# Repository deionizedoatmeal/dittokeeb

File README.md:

# dittokeeb
RP2040 powered keyboard!

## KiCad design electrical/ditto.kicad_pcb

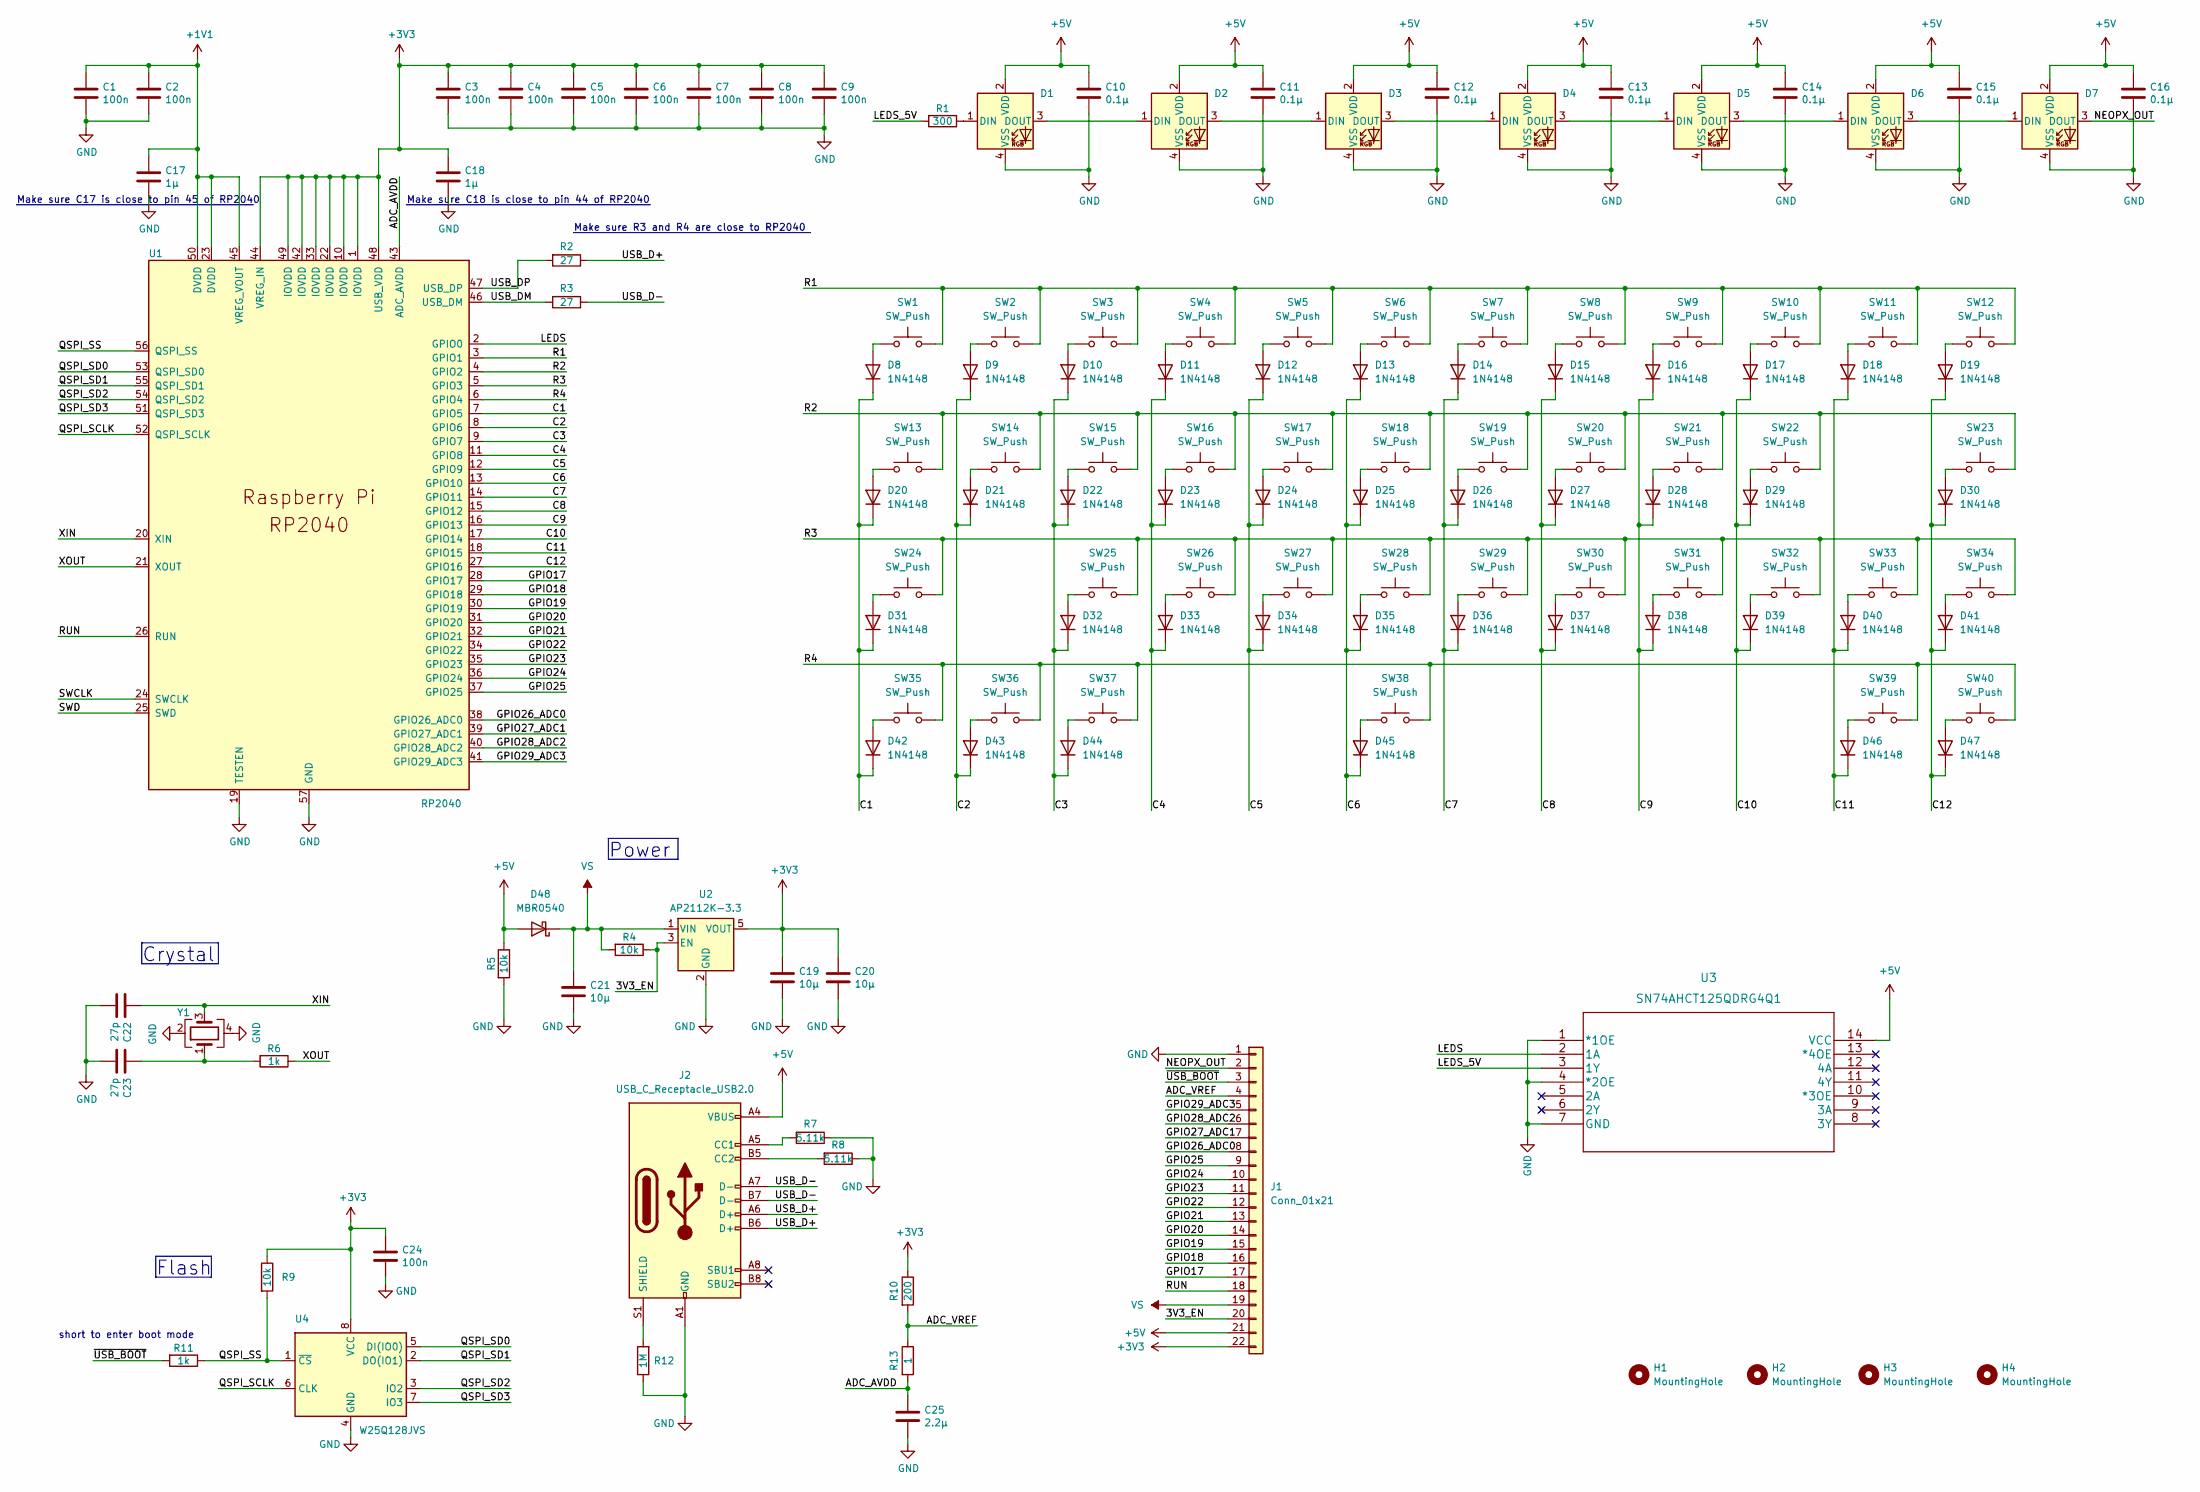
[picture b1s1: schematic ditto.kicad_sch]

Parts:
C1, C2, C3, C4, C5, C6, C7, C8, C9, C24: 100n; C_0402_1005Metric
C10, C11, C12, C13, C14, C15, C16: 0.1µ; C_0805_2012Metric
C17, C18: 1µ; C_0402_1005Metric
C19, C20, C21: 10µ; C_0805_2012Metric
C22, C23: 27p; C_0402_1005Metric
C25: 2.2µ; C_0402_1005Metric
D1, D2, D3, D4, D5, D6, D7: SK6805-EC
D8, D9, D10, D11, D12, D13, D14, D15, D16, D17, D18, D19, D20, D21, D22, D23, D24, D25, D26, D27, D28, D29, D30, D31, D32, D33, D34, D35, D36, D37, D38, D39, D40, D41, D42, D43, D44, D45, D46, D47: 1N4148; D_DO-35_SOD27_P7.62mm_Horizontal
D48: MBR0540; D_SOD-123
H1, H2, H3, H4: MountingHole; MountingHole_2.2mm_M2_DIN965_Pad
J1: Conn_01x21; PinHeader_1x22_P1.00mm_Horizontal
J2: USB_C_Receptacle_USB2.0; USB_C_Receptacle_HRO_TYPE-C-31-M-12
R1: 300; R_0603_1608Metric
R2, R3: 27; C_0402_1005Metric
R4, R5, R9: 10k; C_0402_1005Metric
R6, R11: 1k; C_0402_1005Metric
R7, R8: 5.11k; C_0402_1005Metric
R10: 200; C_0402_1005Metric
R12: 1M; C_0402_1005Metric
R13: 1; C_0402_1005Metric
SW1, SW2, SW3, SW4, SW5, SW6, SW7, SW8, SW9, SW10, SW11, SW12, SW14, SW15, SW16, SW17, SW18, SW19, SW20, SW21, SW22, SW25, SW26, SW27, SW28, SW29, SW30, SW31, SW32, SW34, SW36, SW37: SW_Push; SW_Cherry_MX_1.00u_PCB
SW13, SW33, SW35, SW39, SW40: SW_Push; SW_Cherry_MX_1.25u_PCB
SW23, SW24: SW_Push; SW_Cherry_MX_1.75u_PCB
SW38: SW_Push; SW_Cherry_MX_6.25u_PCB
U1: RP2040; RP2040-QFN-56
U2: AP2112K-3.3; SOT-23-5
U3: SN74AHCT125QDRG4Q1
U4: W25Q128JVS; SOIC-8_5.23x5.23mm_P1.27mm
Y1: Crystal_GND24; Crystal_SMD_3225-4Pin_3.2x2.5mm

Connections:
+1V1: C1.1, C2.1, C17.1, U1.23 (DVDD), U1.45 (VREG_VOUT), U1.50 (DVDD)
+3V3: C3.1, C4.1, C5.1, C6.1, C7.1, C8.1, C9.1, C18.1, C19.1, C20.1, C24.1, J1.22, R9.1, R10.1, U1.1 (IOVDD), U1.10 (IOVDD), U1.22 (IOVDD), U1.33 (IOVDD), U1.42 (IOVDD), U1.44 (VREG_IN), U1.48 (USB_VDD), U1.49 (IOVDD), U2.5 (VOUT), U4.8 (VCC)
+5V: C10.1, C11.1, C12.1, C13.1, C14.1, C15.1, C16.1, D1.2 (VDD), D2.2 (VDD), D3.2 (VDD), D4.2 (VDD), D5.2 (VDD), D6.2 (VDD), D7.2 (VDD), D48.2 (A), J1.21, J2.A4 (VBUS), J2.A9 (VBUS), J2.B4 (VBUS), J2.B9 (VBUS), R5.1, U3.14 (VCC)
/3V3_EN: J1.20, R4.1, U2.3 (EN)
/ADC_AVDD: C25.1, R13.2, U1.43 (ADC_AVDD)
/ADC_VREF: J1.4, R10.2, R13.1
/C1: D8.1 (K), D20.1 (K), D31.1 (K), D42.1 (K), U1.7 (GPIO5)
/C2: D9.1 (K), D21.1 (K), D43.1 (K), U1.8 (GPIO6)
/C3: D10.1 (K), D22.1 (K), D32.1 (K), D44.1 (K), U1.9 (GPIO7)
/C4: D11.1 (K), D23.1 (K), D33.1 (K), U1.11 (GPIO8)
/C5: D12.1 (K), D24.1 (K), D34.1 (K), U1.12 (GPIO9)
/C6: D13.1 (K), D25.1 (K), D35.1 (K), D45.1 (K), U1.13 (GPIO10)
/C7: D14.1 (K), D26.1 (K), D36.1 (K), U1.14 (GPIO11)
/C8: D15.1 (K), D27.1 (K), D37.1 (K), U1.15 (GPIO12)
/C9: D16.1 (K), D28.1 (K), D38.1 (K), U1.16 (GPIO13)
/C10: D17.1 (K), D29.1 (K), D39.1 (K), U1.17 (GPIO14)
/C11: D18.1 (K), D40.1 (K), D46.1 (K), U1.18 (GPIO15)
/C12: D19.1 (K), D30.1 (K), D41.1 (K), D47.1 (K), U1.27 (GPIO16)
/GPIO17: J1.17, U1.28 (GPIO17)
/GPIO18: J1.16, U1.29 (GPIO18)
/GPIO19: J1.15, U1.30 (GPIO19)
/GPIO20: J1.14, U1.31 (GPIO20)
/GPIO21: J1.13, U1.32 (GPIO21)
/GPIO22: J1.12, U1.34 (GPIO22)
/GPIO23: J1.11, U1.35 (GPIO23)
/GPIO24: J1.10, U1.36 (GPIO24)
/GPIO25: J1.9, U1.37 (GPIO25)
/GPIO26_ADC0: J1.8, U1.38 (GPIO26_ADC0)
/GPIO27_ADC1: J1.7, U1.39 (GPIO27_ADC1)
/GPIO28_ADC2: J1.6, U1.40 (GPIO28_ADC2)
/GPIO29_ADC3: J1.5, U1.41 (GPIO29_ADC3)
/LEDS: U1.2 (GPIO0), U3.2 (1A)
/LEDS_5V: R1.2, U3.3 (1Y)
/NEOPX_OUT: D7.3 (DOUT), J1.2
/QSPI_SCLK: U1.52 (QSPI_SCLK), U4.6 (CLK)
/QSPI_SD0: U1.53 (QSPI_SD0), U4.5 (DI(IO0))
/QSPI_SD1: U1.55 (QSPI_SD1), U4.2 (DO(IO1))
/QSPI_SD2: U1.54 (QSPI_SD2), U4.3 (IO2)
/QSPI_SD3: U1.51 (QSPI_SD3), U4.7 (IO3)
/QSPI_SS: R9.2, R11.1, U1.56 (QSPI_SS), U4.1 (~CS)
/R1: SW1.2, SW2.2, SW3.2, SW4.2, SW5.2, SW6.2, SW7.2, SW8.2, SW9.2, SW10.2, SW11.2, SW12.2, U1.3 (GPIO1)
/R2: SW13.2, SW14.2, SW15.2, SW16.2, SW17.2, SW18.2, SW19.2, SW20.2, SW21.2, SW22.2, SW23.2, U1.4 (GPIO2)
/R3: SW24.2, SW25.2, SW26.2, SW27.2, SW28.2, SW29.2, SW30.2, SW31.2, SW32.2, SW33.2, SW34.2, U1.5 (GPIO3)
/R4: SW35.2, SW36.2, SW37.2, SW38.2, SW39.2, SW40.2, U1.6 (GPIO4)
/RUN: J1.18, U1.26 (RUN)
/SWCLK: U1.24 (SWCLK)
/SWD: U1.25 (SWD)
/USB_D+: J2.A6 (D+), J2.B6 (D+), R2.1
/USB_D-: J2.A7 (D-), J2.B7 (D-), R3.1
/USB_DM: R3.2, U1.46 (USB_DM)
/USB_DP: R2.2, U1.47 (USB_DP)
/XIN: C22.1, U1.20 (XIN), Y1.3
/XOUT: R6.1, U1.21 (XOUT)
/~USB_BOOT: J1.3, R11.2
GND: C1.2, C2.2, C3.2, C4.2, C5.2, C6.2, C7.2, C8.2, C9.2, C10.2, C11.2, C12.2, C13.2, C14.2, C15.2, C16.2, C17.2, C18.2, C19.2, C20.2, C21.2, C22.2, C23.2, C24.2, C25.2, D1.4 (VSS), D2.4 (VSS), D3.4 (VSS), D4.4 (VSS), D5.4 (VSS), D6.4 (VSS), D7.4 (VSS), J1.1, J2.A1 (GND), J2.A12 (GND), J2.B1 (GND), J2.B12 (GND), R5.2, R7.1, R8.1, R12.1, U1.19 (TESTEN), U1.57 (GND), U2.2 (GND), U3.1 (*1OE), U3.4 (*2OE), U3.7 (GND), U4.4 (GND), Y1.2, Y1.4
unnamed: C23.1, R6.2, Y1.1
unnamed: D1.1 (DIN), R1.1
unnamed: D1.3 (DOUT), D2.1 (DIN)
unnamed: D2.3 (DOUT), D3.1 (DIN)
unnamed: D3.3 (DOUT), D4.1 (DIN)
unnamed: D4.3 (DOUT), D5.1 (DIN)
unnamed: D5.3 (DOUT), D6.1 (DIN)
unnamed: D6.3 (DOUT), D7.1 (DIN)
unnamed: D8.2 (A), SW1.1
unnamed: D9.2 (A), SW2.1
unnamed: D10.2 (A), SW3.1
unnamed: D11.2 (A), SW4.1
unnamed: D12.2 (A), SW5.1
unnamed: D13.2 (A), SW6.1
unnamed: D14.2 (A), SW7.1
unnamed: D15.2 (A), SW8.1
unnamed: D16.2 (A), SW9.1
unnamed: D17.2 (A), SW10.1
unnamed: D18.2 (A), SW11.1
unnamed: D19.2 (A), SW12.1
unnamed: D20.2 (A), SW13.1
unnamed: D21.2 (A), SW14.1
unnamed: D22.2 (A), SW15.1
unnamed: D23.2 (A), SW16.1
unnamed: D24.2 (A), SW17.1
unnamed: D25.2 (A), SW18.1
unnamed: D26.2 (A), SW19.1
unnamed: D27.2 (A), SW20.1
unnamed: D28.2 (A), SW21.1
unnamed: D29.2 (A), SW22.1
unnamed: D30.2 (A), SW23.1
unnamed: D31.2 (A), SW24.1
unnamed: D32.2 (A), SW25.1
unnamed: D33.2 (A), SW26.1
unnamed: D34.2 (A), SW27.1
unnamed: D35.2 (A), SW28.1
unnamed: D36.2 (A), SW29.1
unnamed: D37.2 (A), SW30.1
unnamed: D38.2 (A), SW31.1
unnamed: D39.2 (A), SW32.1
unnamed: D40.2 (A), SW33.1
unnamed: D41.2 (A), SW34.1
unnamed: D42.2 (A), SW35.1
unnamed: D43.2 (A), SW36.1
unnamed: D44.2 (A), SW37.1
unnamed: D45.2 (A), SW38.1
unnamed: D46.2 (A), SW39.1
unnamed: D47.2 (A), SW40.1
unnamed: J2.A5 (CC1), R7.2
unnamed: J2.B5 (CC2), R8.2
unnamed: J2.S1 (SHIELD), R12.2
VS: C21.1, D48.1 (K), J1.19, R4.2, U2.1 (VIN)

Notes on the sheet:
Crystal
Make sure C17 is close to pin 45 of RP2040
Make sure C18 is close to pin 44 of RP2040
short to enter boot mode
Make sure R3 and R4 are close to RP2040
Power
Flash

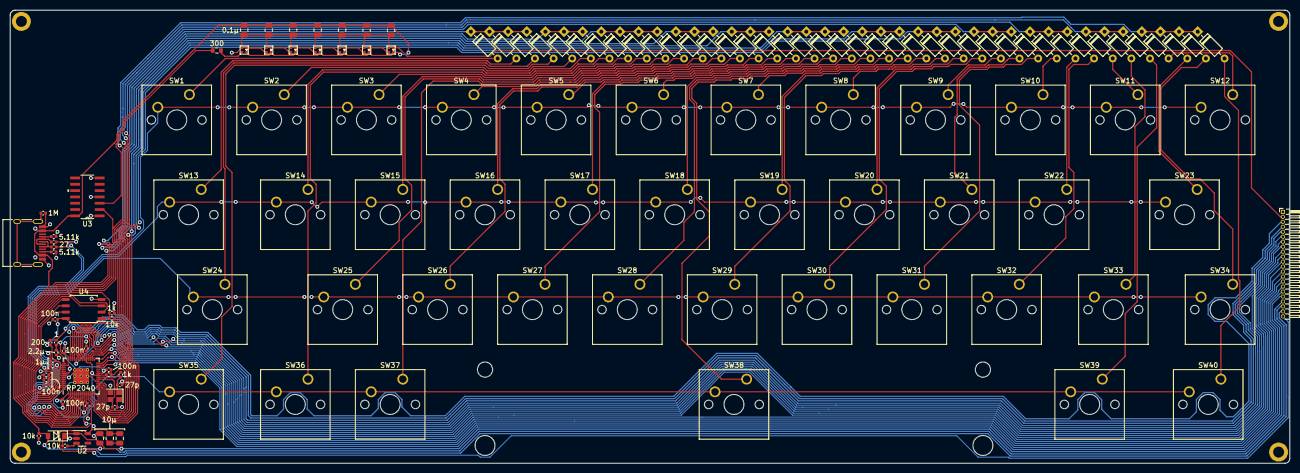
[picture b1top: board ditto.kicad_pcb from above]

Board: 2 copper layers, 257.0 x 91.0 mm, 137 parts (0 on the bottom side), 105 nets.

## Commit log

2022-05-31 inital kicad modeling
2022-06-01 added logic level shifter for neopixels, gerbers, 3d file
2022-06-01 keyboard plate
2022-06-07 STLs for the case, reorganization, etc
2022-06-07 adjustments to case STLs
2022-06-08 added screw holes
2022-06-09 PDFs
2022-06-17 adjusted a few mm on the case tolerances
2022-06-18 inital keeb firmware
2022-06-19 switched libraries
2022-06-20 minor adjustments to the top case dimensions
2022-06-21 keyboard firmware
2022-06-21 ditto facts
2022-06-22 adjusted mating interface on the two top halves
2022-06-22 keystem connector
2022-06-28 adapter from 1mm headers to 2.7mm headers
2022-07-15 added brightness variable
2022-08-25 update layout
